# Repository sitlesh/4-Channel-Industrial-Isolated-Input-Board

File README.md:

# 4-Channel Industrial Isolated Digital Input Board ⚡🏭

This repository contains the complete hardware design, production-ready Gerber files, and simulation models for a professional 4-channel isolated digital input card. It safely interfaces 24V industrial signals (from PLCs, proximity sensors, pushbuttons) with sensitive 3.3V/5V microcontrollers (like STM32, Arduino, or ESP32).

---

## 📸 Visuals & Renders

### 3D View of the Board

### Top Silkscreen & Track Routing

### Gerber Production Preview

---

## 📌 Project Overview
Industrial environments are full of electrical noise, voltage surges, and ground loops. This board provides complete galvanic isolation and transient protection for 4 independent input channels.

### Key Specifications:
- **Input Voltage:** 24V DC nominal (Field Side)
- **Output Logic:** 3.3V Active-Low (Logic Side)
- **PCB Dimensions:** 65mm x 50mm (2-Layer Board)
- **Software Used:** KiCad 8.0 (PCB Design) & LTspice (Circuit Simulation)

---

## 🛠️ Hardware Features & Architecture

### 1. Galvanic Isolation
- Uses **PC817 Optocouplers** to completely separate the 24V Field Circuit from the 3.3V Logic Circuit.
- Features a strict **5mm physical isolation trench** (Creepage distance) across the copper layers to ensure no electrical arcing occurs.

### 2. Circuit Protection
- **SMAJ24CA Transient Voltage Suppressor (TVS) Diodes** are placed directly at the input connectors to clamp high-voltage spikes and surges.
- Input current limiting via large **2512-packaged 1.2kΩ resistors** to safely handle thermal dissipation.

### 3. Visual Indicators
- Each channel includes a low-power **1206 status LED** for instant visual debugging on the factory floor.

---

## 📊 LTspice Simulation & Logic
Before layout execution, the circuit logic was thoroughly verified using **LTspice Transient Analysis**. 
- **Inverted Logic:** When a 24V input is detected (HIGH), the optocoupler transistor pulls the MCU pin to 0V (LOW). When the input is disconnected (LOW), the 4.7kΩ pull-up resistor pulls the pin to 3.3V (HIGH).

---

## 📁 Repository File Guide
*Click on the links below to view the source files directly inside GitHub:*

* 📄 **[Schematic File (.kicad_sch)](Industrial%204-Channel%20Isolated%20Digital%20Input%20Output%20Board.kicad_sch)** - Circuit schematics, component ratings, and connections.
* 🎛️ **[PCB Layout File (.kicad_pcb)](Industrial%204-Channel%20Isolated%20Digital%20Input%20Output%20Board.kicad_pcb)** - 2-layer track routing, ground planes, and component placements.
* 📦 **[Production Gerbers (.zip)](Gerbers.zip)** - Manufacture-ready fabrication files (Gerber + Drill data).
* 📁 **[Images Directory](/Images)** - Folder containing the 3D renders and layouts used in this readme.

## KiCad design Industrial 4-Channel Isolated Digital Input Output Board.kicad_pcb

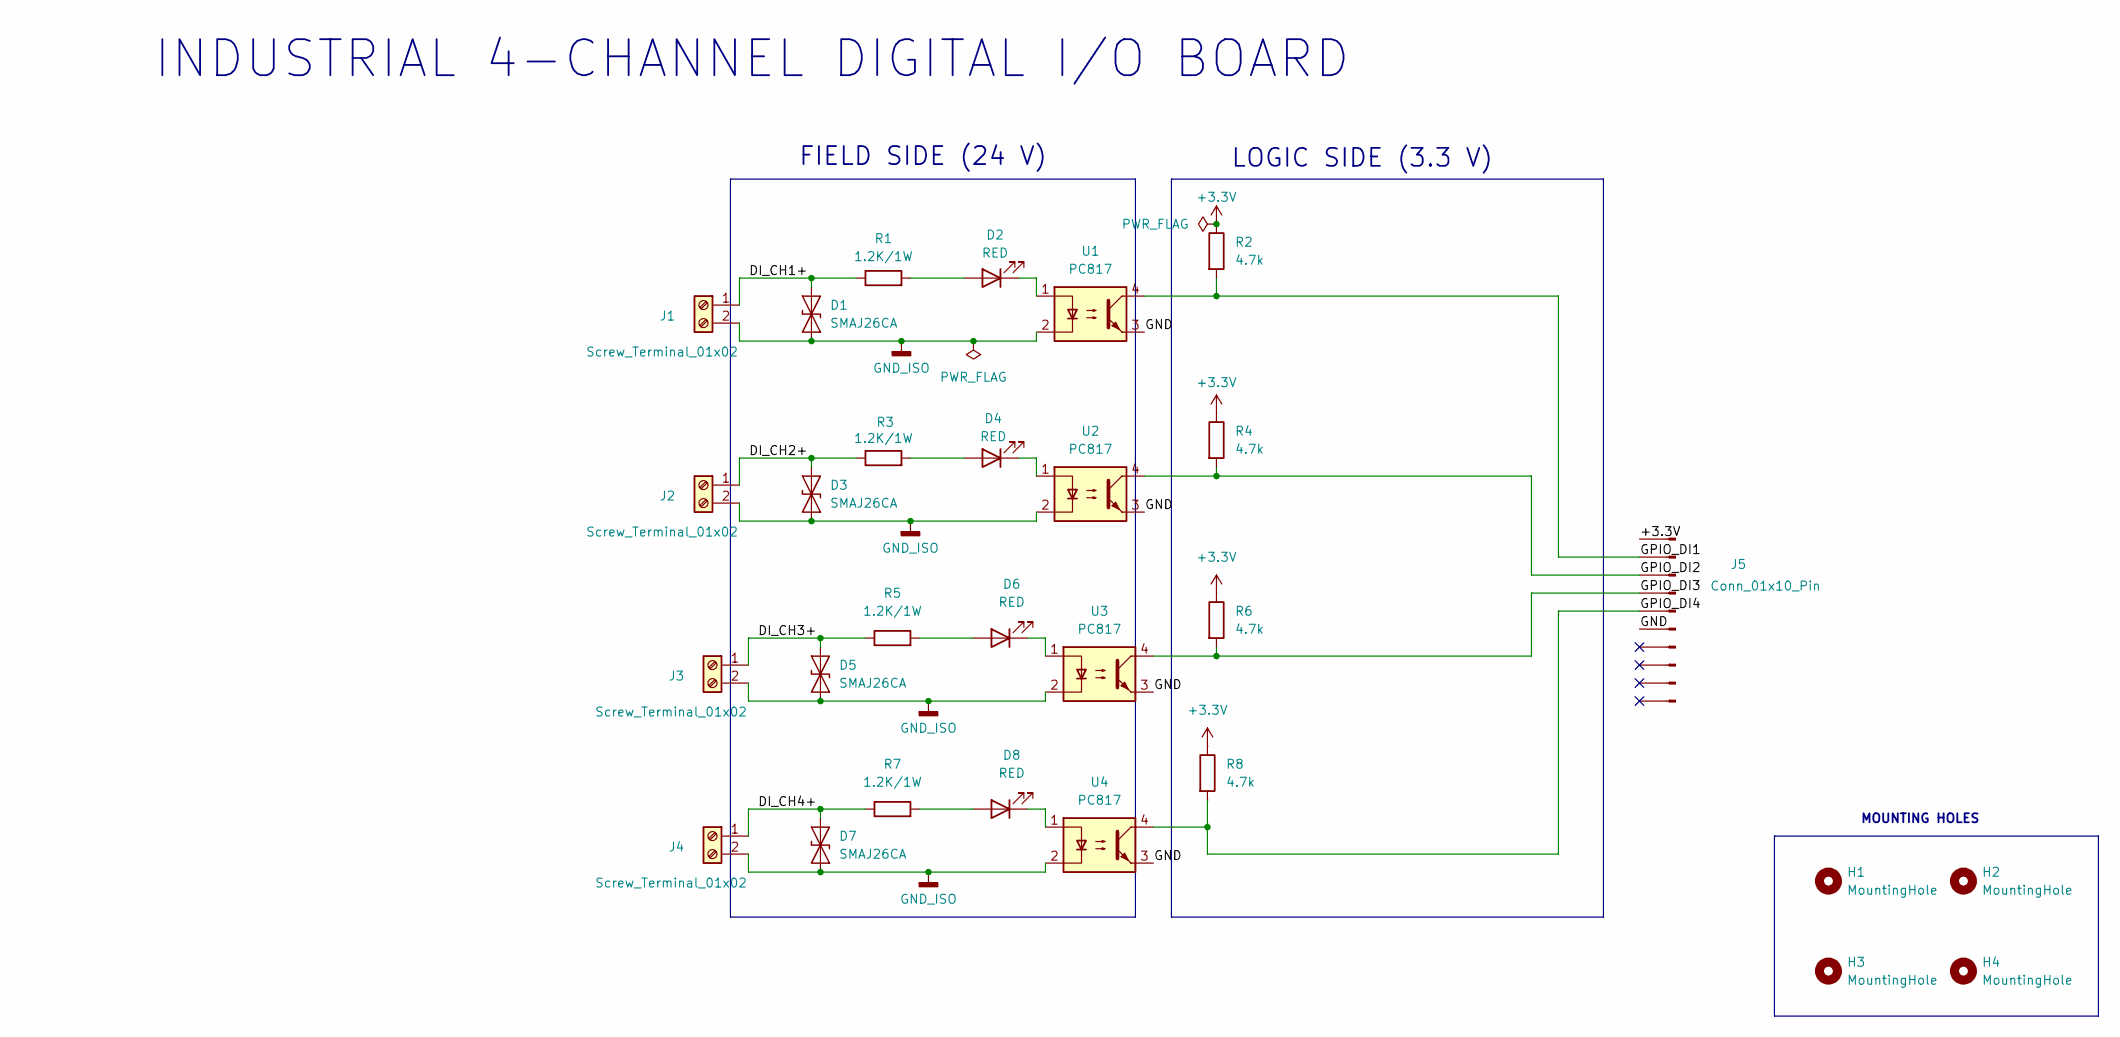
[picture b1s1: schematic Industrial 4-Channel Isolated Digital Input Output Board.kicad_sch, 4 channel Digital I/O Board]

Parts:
D1, D3, D5, D7: SMAJ26CA; D_SMA
D2, D4, D6, D8: RED; LED_1206_3216Metric
H1, H2, H3, H4: MountingHole; MountingHole_3.2mm_M3
J1, J2, J3, J4: Screw_Terminal_01x02; TerminalBlock_Phoenix_PT-1,5-2-3.5-H_1x02_P3.50mm_Horizontal
J5: Conn_01x10_Pin; PinHeader_1x10_P2.54mm_Vertical
R1, R3, R5, R7: 1.2K/1W; R_2512_6332Metric
R2, R4, R6, R8: 4.7k; R_0805_2012Metric
U1, U2, U3, U4: PC817; DIP-4_W7.62mm

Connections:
+3.3V: J5.1, R2.1, R4.1, R6.1, R8.1
/DI_CH1+: D1.2 (A2), J1.1, R1.1
/DI_CH2+: D3.2 (A2), J2.1, R3.1
/DI_CH3+: D5.2 (A2), J3.1, R5.1
/DI_CH4+: D7.2 (A2), J4.1, R7.1
/GND: J5.6, U1.3, U2.3, U3.3, U4.3
/GPIO_DI1: J5.2, R2.2, U1.4
/GPIO_DI2: J5.3, R4.2, U2.4
/GPIO_DI3: J5.4, R6.2, U3.4
/GPIO_DI4: J5.5, R8.2, U4.4
GND_ISO: D1.1 (A1), D3.1 (A1), D5.1 (A1), D7.1 (A1), J1.2, J2.2, J3.2, J4.2, U1.2, U2.2, U3.2, U4.2
unnamed: D2.2 (A), R1.2
unnamed: D2.1 (K), U1.1
unnamed: D4.2 (A), R3.2
unnamed: D4.1 (K), U2.1
unnamed: D6.2 (A), R5.2
unnamed: D6.1 (K), U3.1
unnamed: D8.2 (A), R7.2
unnamed: D8.1 (K), U4.1

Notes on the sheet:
FIELD SIDE (24 V)
MOUNTING HOLES
LOGIC SIDE (3.3 V)
INDUSTRIAL 4-CHANNEL DIGITAL I/O BOARD

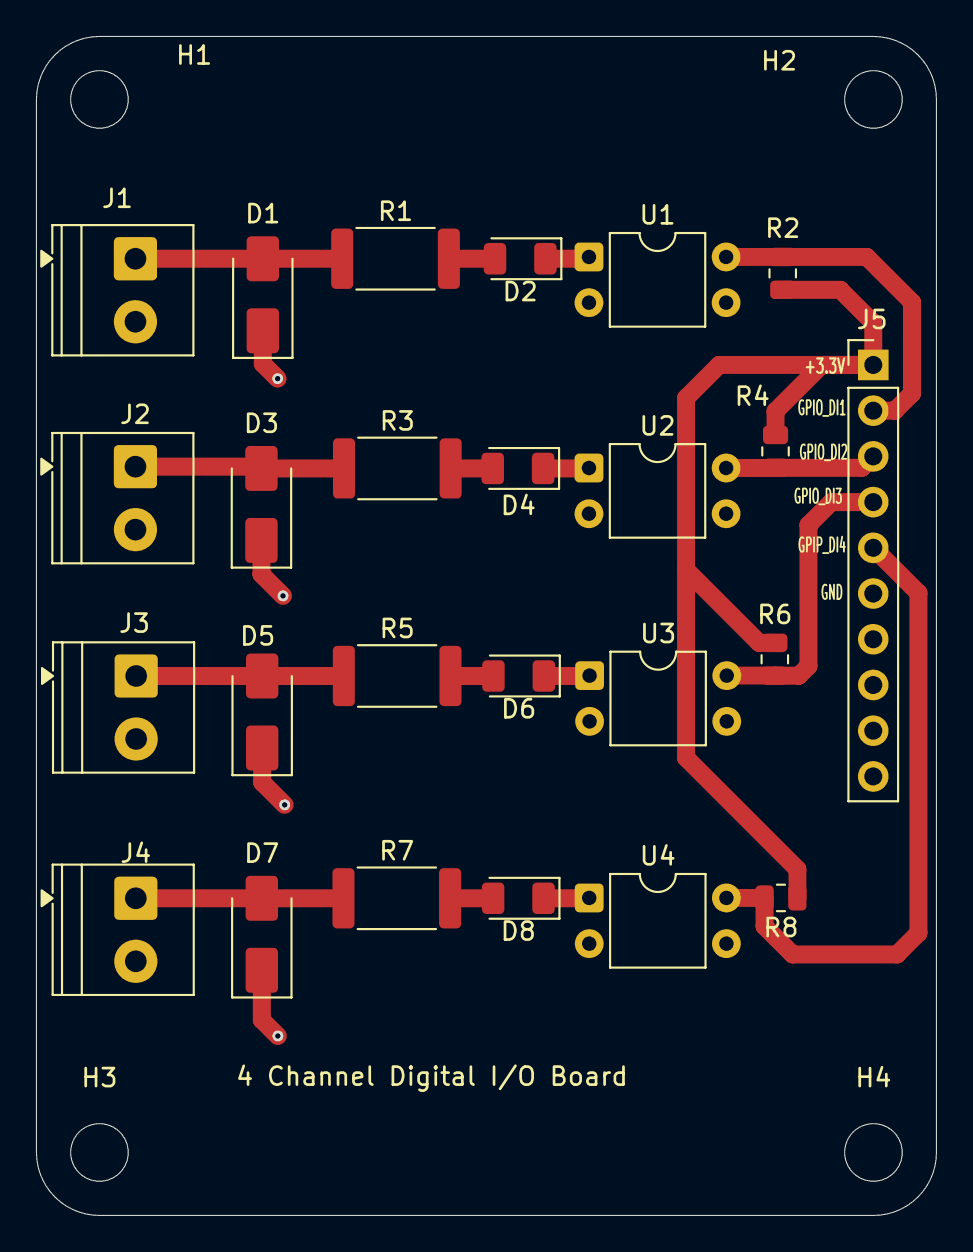
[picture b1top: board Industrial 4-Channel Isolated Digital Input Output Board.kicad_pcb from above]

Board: 2 copper layers, 50.0 x 65.5 mm, 29 parts (0 on the bottom side), 19 nets.

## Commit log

2026-06-02 Rename Industrial 4-Channel Isolated Digital Input Output Board.png to 3D view
2026-06-02 Rename 3D view to 3D view.png
2026-06-02 Rename Screenshot (49).png to F.Silkscreen.png
2026-06-02 Rename Screenshot (50).png to Gerber view.png
